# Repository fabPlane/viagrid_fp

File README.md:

# viagrid_fp
Viagrid example projects

This repository contains **10 introductory [Viagrid](https://viagrid.io) circuit board designs** covering fundamental PCB concepts. Each board is stored as a JSON file in the `boards/` directory and can be opened directly in Viagrid.

---

## Boards

| # | File | Description |
|---|------|-------------|
| 01 | [LED Blinker](boards/01_led_blinker.json) | 555-timer astable oscillator driving a red LED. Introduces RC timing, decoupling caps, and output current limiting. |
| 02 | [Push-Button LED](boards/02_push_button_led.json) | Tactile switch → current-limiting resistor → LED. The simplest possible complete circuit; includes a 100 nF debounce cap. |
| 03 | [3.3 V Buck Regulator](boards/03_buck_regulator_3v3.json) | XL4005 step-down switcher (5–40 V in → 3.3 V / 2 A out). Covers feedback dividers, flyback diode, and output capacitor sizing. |
| 04 | [Arduino Nano Breakout](boards/04_arduino_nano_breakout.json) | Clean breakout board exposing all Nano I/O pins on 0.1″ headers with barrel-jack power, decoupling caps, and M3 mounting holes. |
| 05 | [USB-C PD Sink](boards/05_usb_c_pd_sink.json) | CH224K PD negotiation IC requests 9 V or 12 V from a USB-C charger. Demonstrates CC resistors, TVS protection, and DIP-switch voltage selection. |
| 06 | [H-Bridge Motor Driver](boards/06_h_bridge_motor_driver.json) | L298N dual H-bridge for bidirectional DC motor or stepper control. Covers PWM inputs, flyback diodes, and isolated motor/logic power domains. |
| 07 | [Temp & Humidity Sensor Node](boards/07_temp_humidity_sensor_node.json) | ESP8266 (Wemos D1 Mini) + DHT22 with TP4056 LiPo charger and 3.3 V LDO. Teaches sensor pull-ups, battery management, and low-power Wi-Fi. |
| 08 | [RS-485 Isolated Transceiver](boards/08_rs485_isolated_transceiver.json) | MAX485 with PC817 opto-isolation for Modbus RTU. Shows bus termination, fail-safe bias resistors, and isolated power planes. |
| 09 | [Raspberry Pi HAT – GPIO & RTC](boards/09_rpi_hat_gpio_rtc.json) | MCP23017 I²C GPIO expander + DS3231 RTC + AT24C32 EEPROM on a standard RPi HAT form factor. Covers I²C addressing, battery backup, and HAT compliance. |
| 10 | [Class-D Audio Amplifier](boards/10_class_d_audio_amplifier.json) | PAM8403 stereo 3 W×2 amplifier with log-pot volume control, input coupling caps, and ferrite-bead EMI filters on speaker outputs. |

---

## How to use

1. Open [viagrid.io](https://viagrid.io) in your browser.
2. Create a new board or select *Import*.
3. Upload the desired `.json` file from the `boards/` directory.
4. The schematic, net list, and component placements will load automatically.

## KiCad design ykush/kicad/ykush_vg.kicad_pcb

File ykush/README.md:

# YKUSH-VG: 3-port switchable USB 2.0 hub on a Viagrid 9055 blank

A board that works like the [Yepkit YKUSH](https://www.yepkit.com/products/ykush), laid out for a
2-layer [Viagrid](https://github.com/opulo-inc/viagrid) 9055 blank.

- **Hub:** Terminus FE1.1s (SSOP-28). Upstream port is USB-C. Ports 1-3 go to the USB-A sockets,
  and port 4 goes to the control MCU.
- **Control:** WCH CH552G. The host sees it as a HID device. The plan is for its firmware to speak
  the YKUSH protocol, so `ykushcmd` works unchanged.
- **Port power:** one SY6280AAC current-limited switch per port. The CH552G drives each EN pin,
  and each EN has a 100k pull-down so the port stays off during boot.
- **Power:** from upstream VBUS, or from an external 5 V screw terminal. The two sources are
  diode-ORed onto `+5V_PORT`.

| File | What |
|---|---|
| `FEASIBILITY.md` | Why this is doable on Viagrid, and the risks |
| `kicad/ykush_vg.kicad_pro` / `.kicad_sch` | KiCad 10 project and schematic (generated) |
| `kicad/ykush_vg.kicad_sym`, `kicad/sym-lib-table` | Project symbol library (CH552G, SY6280AAC) |
| `kicad/ykush_vg_schematic.pdf` | PDF of the schematic |
| `kicad/bom.md`, `kicad/bom.csv` | BOM with Shopee/Lazada, AliExpress, DigiKey and JLCPCB columns |
| `kicad/nets.txt` | Netlist the generator intended |
| `tools/make_schematic.py` | **Source of truth.** Edit this, then regenerate |
| `tools/check_netlist.py` | Exports the netlist with kicad-cli and diffs it against `nets.txt` |
| `kicad/ykush_vg.kicad_pcb` | The PCB, generated by `tools/build_pcb.py` (see `pcb/LAYOUT.md`) |
| `firmware/` | CH552G firmware (SDCC), tests, host tool, udev rule |
| `fab/` | Laser DXFs, Gerbers, drill file, `holes_to_drill.csv`, placement file, previews |

```sh
cd tools && python3 make_schematic.py && python3 check_netlist.py
kicad-cli sch erc --severity-all ../kicad/ykush_vg.kicad_sch
```

Needs KiCad 10. The generator reads the KiCad 10 symbol libraries and then runs
`kicad-cli sch upgrade`, so the saved file is in KiCad's native format.

## Status
- [x] Schematic. Pinouts checked against the FE1.1s, CH552 and SY6280 datasheets, and against
  open-source boards.
- [x] BOM and sourcing
- [x] ERC in KiCad 10.0.6: 0 violations (all severities)
- [x] PCB layout on the Viagrid 9055 blank: fully routed. KiCad 10 DRC reports 0 errors,
  0 unconnected items and 0 schematic mismatches (details in `pcb/LAYOUT.md`).
- [x] Fabrication outputs in `fab/`: copper DXF for LightBurn, Gerbers, and the holes to drill
- [x] CH552 firmware (`firmware/`): YKUSH protocol with YKUSH USB IDs, so `ykushcmd` works.
  It builds to about 2.5 KB and passes descriptor, unit and `ykushcmd` end-to-end tests. It has not
  yet run on real hardware.
- [ ] Build and test a real board

## CH552G pin map (for the firmware)

| Function | CH552G pin |
|---|---|
| USB D+ / D- (hub port 4, Full-Speed) | P3.6 / P3.7 |
| EN port 1 (J2, left) | P1.4 |
| EN port 2 (J3, middle) | P3.3 |
| EN port 3 (J4, right) | P3.4 |
| Status LED (active high) | P3.2 |
| BOOT button (UDP pull-up at power-on) | P3.6 via 10k |

The EN pins are active high. Each has a 100k pull-down, so the ports stay off until the
firmware drives them.

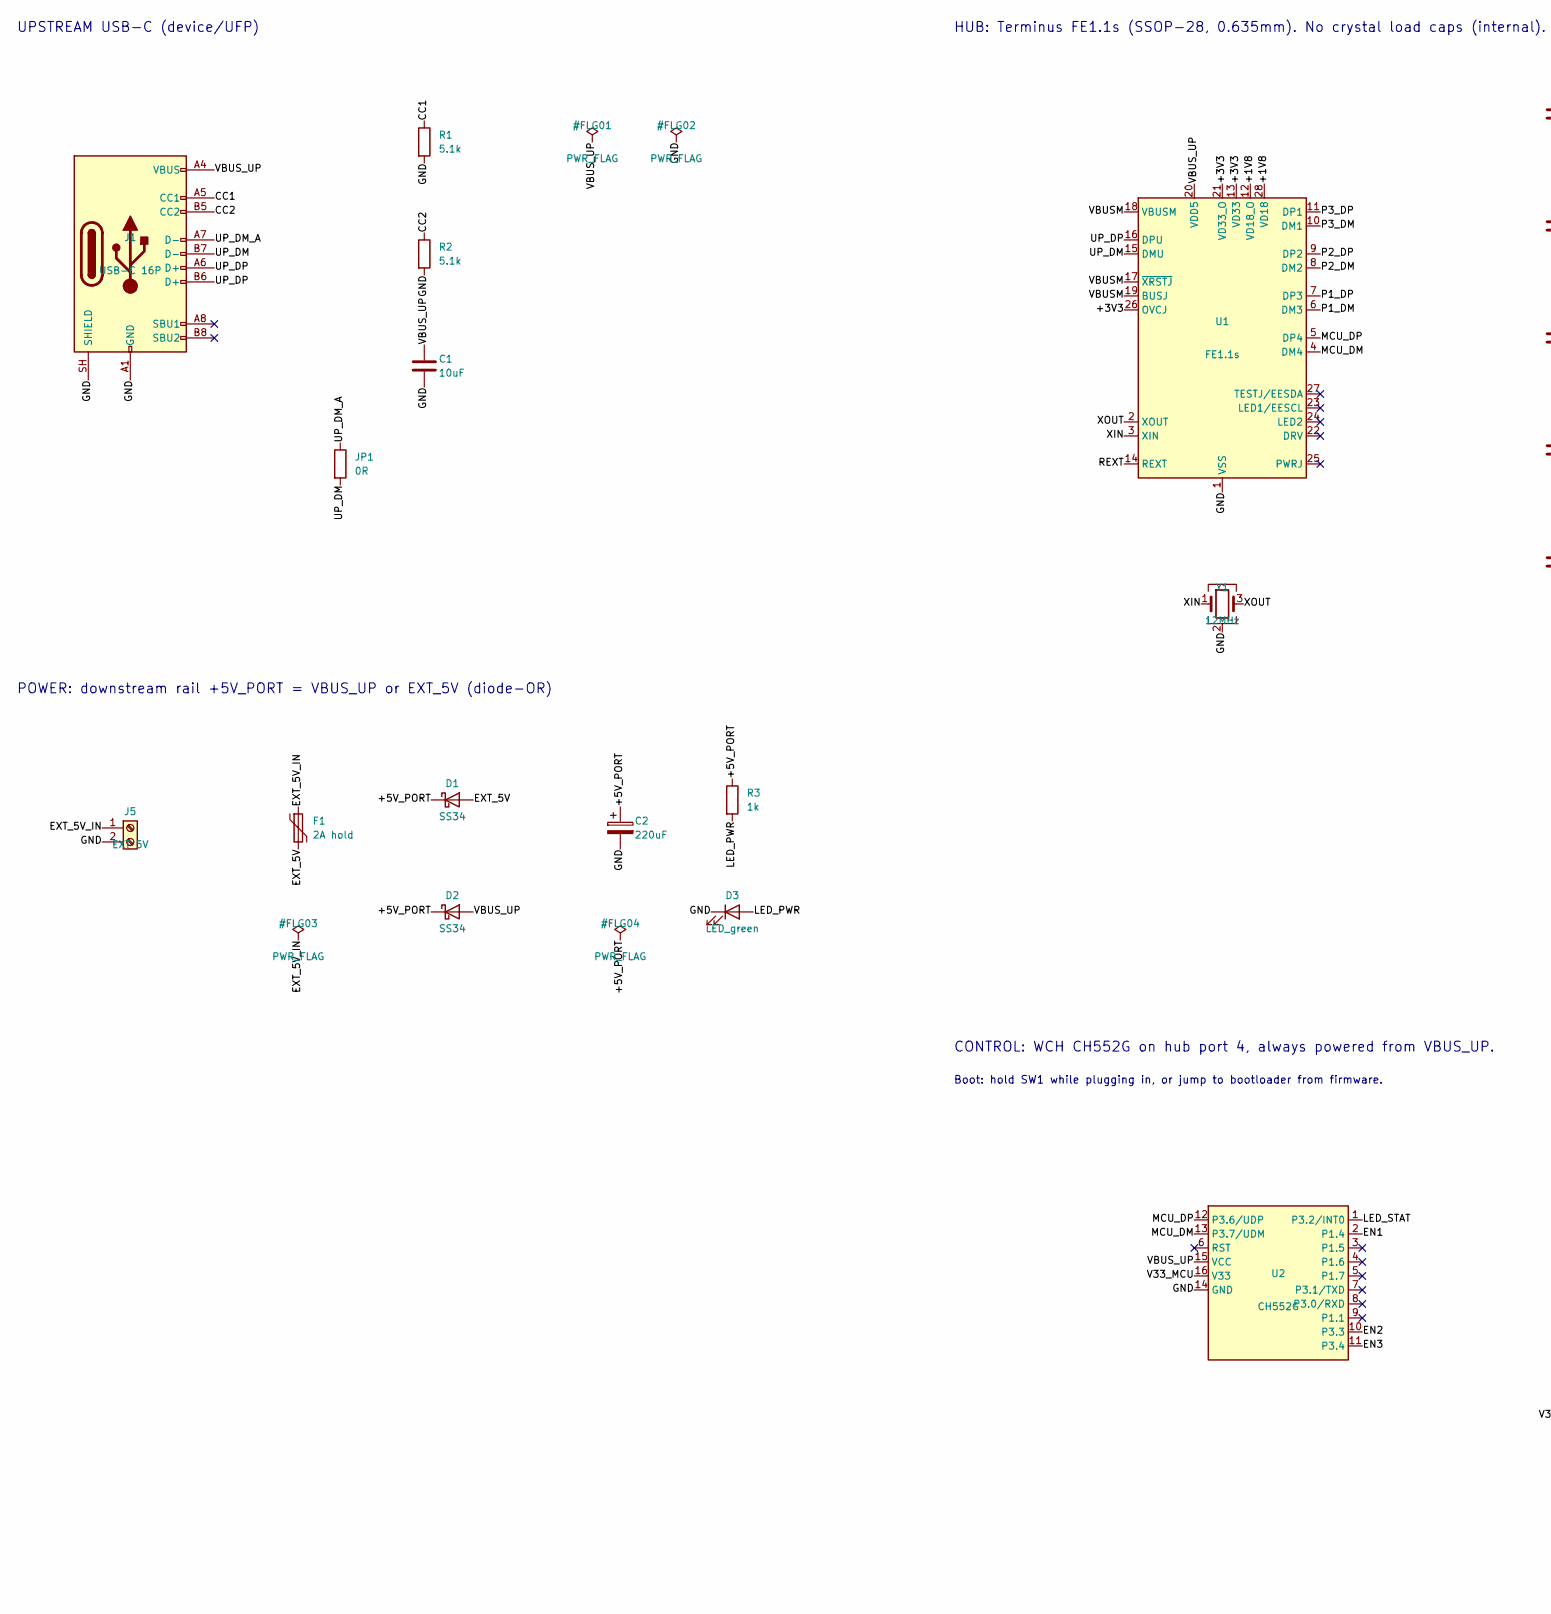
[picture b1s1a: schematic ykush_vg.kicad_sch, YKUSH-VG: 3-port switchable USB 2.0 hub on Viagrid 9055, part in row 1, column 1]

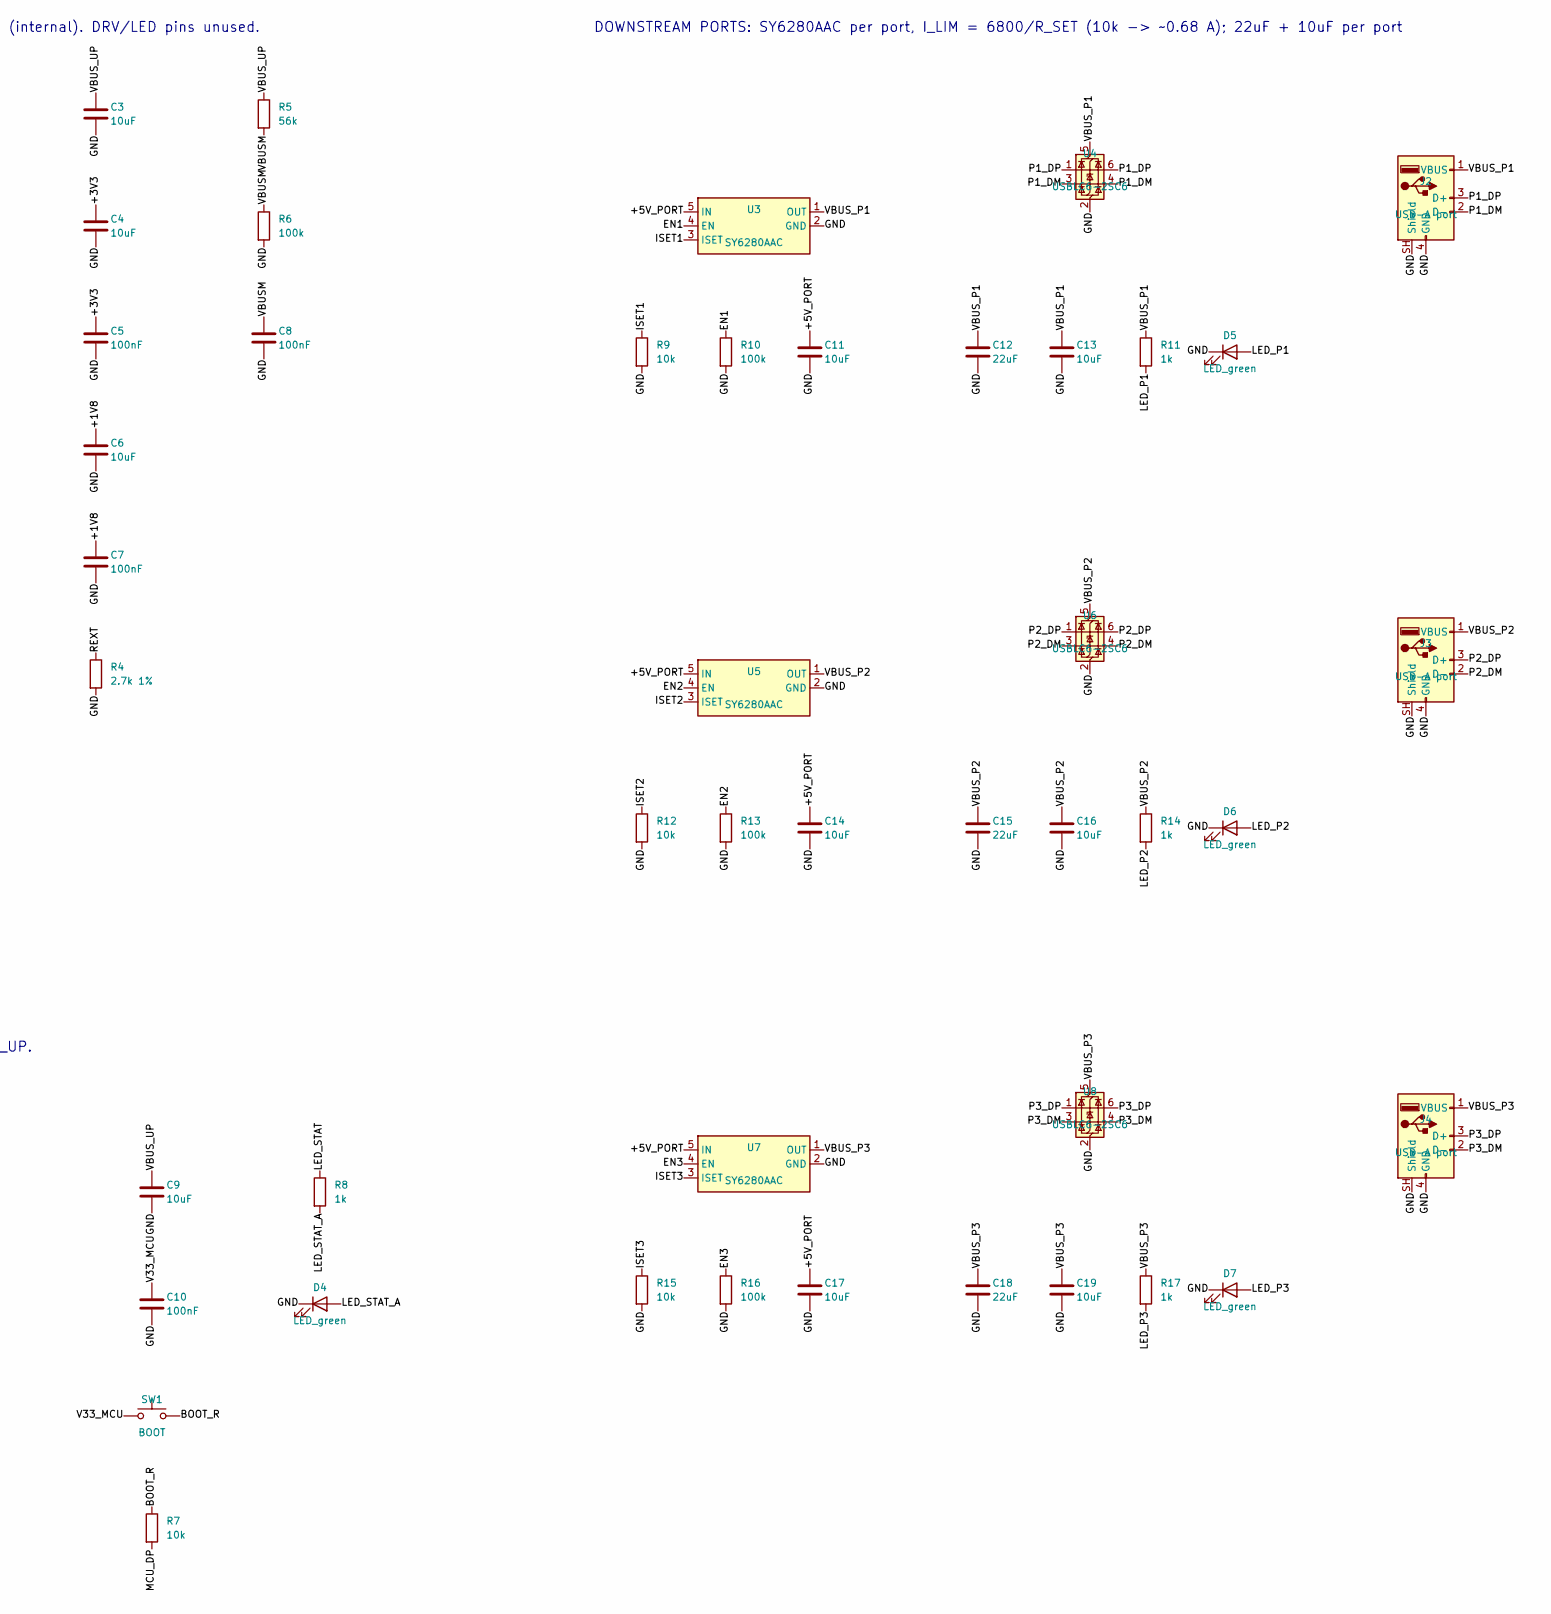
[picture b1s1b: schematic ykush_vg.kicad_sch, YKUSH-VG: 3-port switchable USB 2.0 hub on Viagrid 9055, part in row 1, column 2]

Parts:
C1, C3, C4, C6, C9, C11, C13, C14, C16, C17, C19: 10uF; C_0805_2012Metric
C2: 220uF; CP_Elec_6.3x7.7
C5, C7, C8, C10: 100nF; C_0603_1608Metric
C12, C15, C18: 22uF; C_1206_3216Metric
D1, D2: SS34; D_SMA
D3, D4, D5, D6, D7: LED_green; LED_0805_2012Metric
F1: 2A hold; Fuse_1812_4532Metric
J1: USB-C 16P; USB_C_Receptacle_HRO_TYPE-C-31-M-12
J2, J3, J4: USB-A port; USB_A_TE_292303-7_Horizontal
J5: EXT 5V; TerminalBlock_Phoenix_MKDS-1,5-2-5.08_1x02_P5.08mm_Horizont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
JP1: 0R; R_0603_1608Metric
R1, R2: 5.1k; R_0603_1608Metric
R3, R8, R11, R14, R17: 1k; R_0603_1608Metric
R4: 2.7k 1%; R_0603_1608Metric
R5: 56k; R_0603_1608Metric
R6, R10, R13, R16: 100k; R_0603_1608Metric
R7, R9, R12, R15: 10k; R_0603_1608Metric
SW1: BOOT; SW_Push_1P1T_XKB_TS-1187A
U1: FE1.1s; SSOP-28_3.9x9.9mm_P0.635mm
U2: CH552G; SOIC-16_3.9x9.9mm_P1.27mm
U3, U5, U7: SY6280AAC; SOT-23-5
U4, U6, U8: USBLC6-2SC6; SOT-23-6
Y1: 12MHz; Crystal_SMD_3225-4Pin_3.2x2.5mm

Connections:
/+1V8: C6.1, C7.1, U1.12 (VD18_O), U1.28 (VD18)
/+3V3: C4.1, C5.1, U1.13 (VD33), U1.21 (VD33_O), U1.26 (OVCJ)
/+5V_PORT: C2.1, C11.1, C14.1, C17.1, D1.1 (K), D2.1 (K), R3.1, U3.5 (IN), U5.5 (IN), U7.5 (IN)
/BOOT_R: R7.1, SW1.2
/CC1: J1.A5 (CC1), R1.1
/CC2: J1.B5 (CC2), R2.1
/EN1: R10.1, U2.2 (P1.4), U3.4 (EN)
/EN2: R13.1, U2.10 (P3.3), U5.4 (EN)
/EN3: R16.1, U2.11 (P3.4), U7.4 (EN)
/EXT_5V: D1.2 (A), F1.2
/EXT_5V_IN: F1.1, J5.1
/GND: C1.2, C2.2, C3.2, C4.2, C5.2, C6.2, C7.2, C8.2, C9.2, C10.2, C11.2, C12.2, C13.2, C14.2, C15.2, C16.2, C17.2, C18.2, C19.2, D3.1 (K), D4.1 (K), D5.1 (K), D6.1 (K), D7.1 (K), J1.A1 (GND), J1.A12 (GND), J1.B1 (GND), J1.B12 (GND), J1.SH (SHIELD), J2.4 (GND), J2.SH (Shield), J3.4 (GND), J3.SH (Shield), J4.4 (GND), J4.SH (Shield), J5.2, R1.2, R2.2, R4.2, R6.2, R9.2, R10.2, R12.2, R13.2, R15.2, R16.2, U1.1 (VSS), U2.14 (GND), U3.2 (GND), U4.2 (GND), U5.2 (GND), U6.2 (GND), U7.2 (GND), U8.2 (GND), Y1.2 (G), Y1.4 (G)
/ISET1: R9.1, U3.3 (ISET)
/ISET2: R12.1, U5.3 (ISET)
/ISET3: R15.1, U7.3 (ISET)
/LED_P1: D5.2 (A), R11.2
/LED_P2: D6.2 (A), R14.2
/LED_P3: D7.2 (A), R17.2
/LED_PWR: D3.2 (A), R3.2
/LED_STAT: R8.1, U2.1 (P3.2/INT0)
/LED_STAT_A: D4.2 (A), R8.2
/MCU_DM: U1.4 (DM4), U2.13 (P3.7/UDM)
/MCU_DP: R7.2, U1.5 (DP4), U2.12 (P3.6/UDP)
/P1_DM: J2.2 (D-), U1.6 (DM3), U4.3 (I/O2), U4.4 (I/O2)
/P1_DP: J2.3 (D+), U1.7 (DP3), U4.1 (I/O1), U4.6 (I/O1)
/P2_DM: J3.2 (D-), U1.8 (DM2), U6.3 (I/O2), U6.4 (I/O2)
/P2_DP: J3.3 (D+), U1.9 (DP2), U6.1 (I/O1), U6.6 (I/O1)
/P3_DM: J4.2 (D-), U1.10 (DM1), U8.3 (I/O2), U8.4 (I/O2)
/P3_DP: J4.3 (D+), U1.11 (DP1), U8.1 (I/O1), U8.6 (I/O1)
/REXT: R4.1, U1.14 (REXT)
/UP_DM: J1.B7 (D-), JP1.2, U1.15 (DMU)
/UP_DM_A: J1.A7 (D-), JP1.1
/UP_DP: J1.A6 (D+), J1.B6 (D+), U1.16 (DPU)
/V33_MCU: C10.1, SW1.1, U2.16 (V33)
/VBUSM: C8.1, R5.2, R6.1, U1.17 (~XRSTJ), U1.18 (VBUSM), U1.19 (BUSJ)
/VBUS_P1: C12.1, C13.1, J2.1 (VBUS), R11.1, U3.1 (OUT), U4.5 (VBUS)
/VBUS_P2: C15.1, C16.1, J3.1 (VBUS), R14.1, U5.1 (OUT), U6.5 (VBUS)
/VBUS_P3: C18.1, C19.1, J4.1 (VBUS), R17.1, U7.1 (OUT), U8.5 (VBUS)
/VBUS_UP: C1.1, C3.1, C9.1, D2.2 (A), J1.A4 (VBUS), J1.A9 (VBUS), J1.B4 (VBUS), J1.B9 (VBUS), R5.1, U1.20 (VDD5), U2.15 (VCC)
/XIN: U1.3 (XIN), Y1.1
/XOUT: U1.2 (XOUT), Y1.3

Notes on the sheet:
HUB: Terminus FE1.1s (SSOP-28, 0.635mm). No crystal load caps (internal). DRV/LED pins unused.
UPSTREAM USB-C (device/UFP)
POWER: downstream rail +5V_PORT = VBUS_UP or EXT_5V (diode-OR)
DOWNSTREAM PORTS: SY6280AAC per port, I_LIM = 6800/R_SET (10k -> ~0.68 A); 22uF + 10uF per port
Boot: hold SW1 while plugging in, or jump to bootloader from firmware.
CONTROL: WCH CH552G on hub port 4, always powered from VBUS_UP.

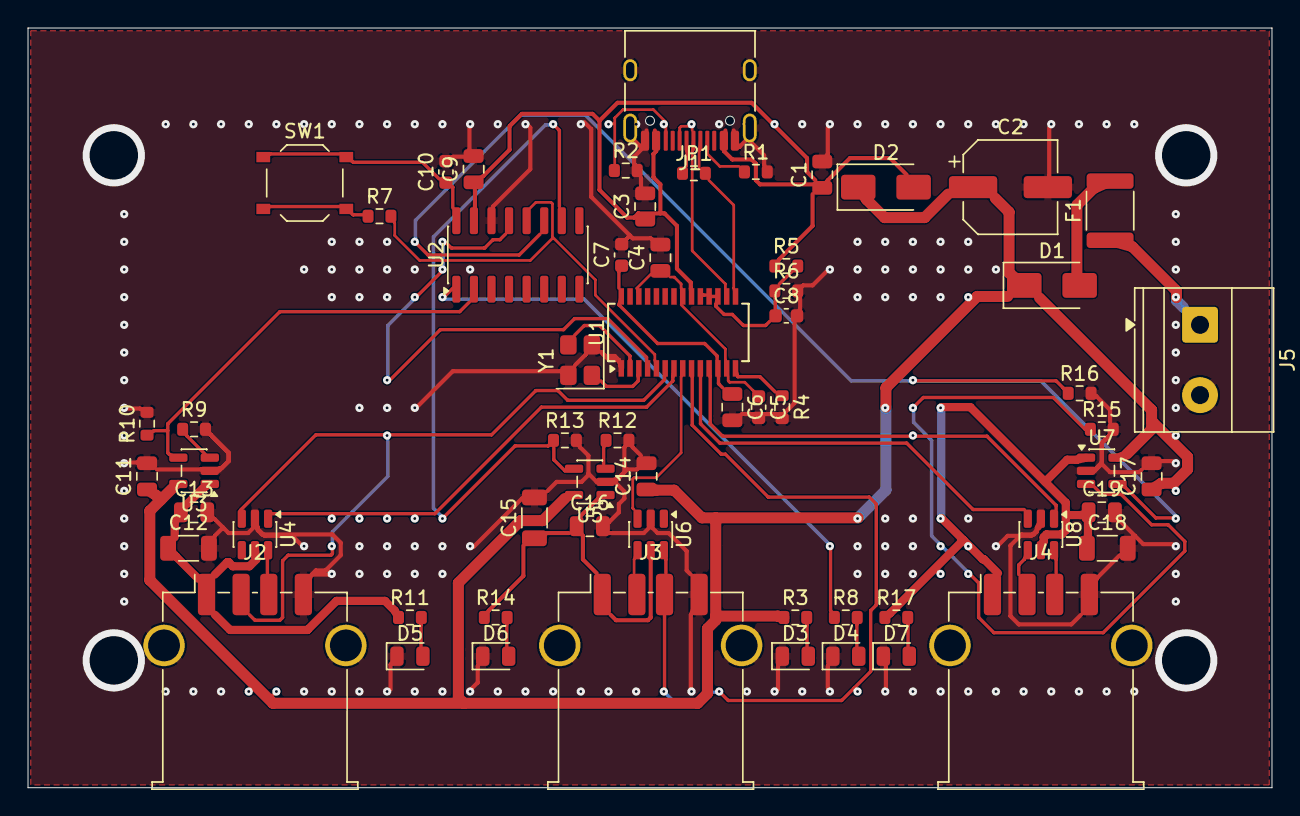
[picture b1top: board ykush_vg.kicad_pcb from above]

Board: 2 copper layers, 89.9 x 54.9 mm, 60 parts (0 on the bottom side), 41 nets.

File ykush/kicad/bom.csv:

#,Refs,Qty,Part,Footprint,Shopee / Lazada (Thailand),AliExpress,DigiKey,JLCPCB (LCSC #),JLC type,Notes
1,U1,1,Terminus FE1.1S-BSOP28 (USB 2.0 HS 4-port hub),SSOP-28_3.9x9.9mm_P0.635mm,YES - Shopee TH (5 pcs),YES,"NO (alt: Microchip USB2514B-AEZC-TR, QFN-36)",C9359,Extended,Buy genuine Rev B (FE1.1S-BSOP28). Cross-border seller: 1-2 weeks.
2,U2 U5 U7 U9,4,ST USBLC6-2SC6 USB ESD array,SOT-23-6,"YES - Shopee TH, Lazada TH",YES,497-5235-1-ND,C7519,Extended,
3,U3,1,"WCH CH552G (SOP-16 MCU, USB device)",SOIC-16_3.9x9.9mm_P1.27mm,YES - Shopee TH (variant in WCH multi-chip listing),YES,NO (alt: PIC16F1455-I/SL; needs different firmware),C111292,Extended,Blank chips boot into the USB bootloader.
4,U4 U6 U8,3,Silergy SY6280AAC load switch,SOT-23-5,NO (MT9700 is on Shopee TH; verify pinout before substituting),YES,"NO (alt: TI TPS2051BDBVR, different pinout)",C55136,Extended,Order from AliExpress/LCSC. Not SY6280AAAC (C207620).
5,Y1,1,YXC X322512MSB4SI 12 MHz 3225 4-pad,Crystal_SMD_3225-4Pin_3.2x2.5mm,NO (only HC-49 seen),YES,Abracon ABM8-12.000MHZ-B2-T (535-9826-1-ND),C9002,Basic,"Passive crystal, not an oscillator. FE1.1s has internal load caps."
6,J1,1,HRO TYPE-C-31-M-12 (USB 2.0 16-pin),USB_C_Receptacle_HRO_TYPE-C-31-M-12,"YES - Shopee TH (TYPE-C-31-M-12), Lazada TH (16P)",YES,"NO (alt: GCT USB4105-GF-A, 2073-USB4105-GF-ACT-ND)",C165948,Extended,Shell pegs need drilled holes on a Viagrid.
7,J2 J3 J4,3,"TE 292303-7 USB-A receptacle, right angle, SMT signal pins",USB_A_TE_292303-7_Horizontal,NO (TH has generic THT 4-pin 90deg; different footprint),LIKELY,TE 292303-7,(search LCSC),Extended,SMT signal pads keep the Viagrid build simple; only the 2 shell tabs need holes.
8,J5,1,Screw terminal 2P 5.08 mm (KF301-2P),"TerminalBlock_Phoenix_MKDS-1,5-2-5.08_1x02_P5.08mm_Horizontal","YES - Shopee TH, Lazada TH, Cybertice, MyArduino",YES,Phoenix 1935161 (277-1667-ND),C474881,Extended,"THT: drill 2 holes, solder from the bottom."
9,SW1,1,Tactile switch 5.1x5.1 mm SMD (XKB TS-1187A-B-A-B),SW_Push_1P1T_XKB_TS-1187A,NO (only 3x4 / 4.5x4.5 / 6x6 seen),YES,C&K PTS810 SJM 250 SMTR LFS,C318884,Basic,Hold while plugging in = CH552 bootloader.
10,F1,1,"PTC resettable fuse 1812, 2 A hold",Fuse_1812_4532Metric,YES - Shopee TH (PPTC kit incl. 1812),YES,Littelfuse 1812L200/12DR,C315901,Extended,
11,D1 D2,2,"SS34 Schottky 3 A 40 V, SMA",D_SMA,YES - Shopee TH (ships from Thailand),YES,Vishay SSA34-E3/61T,C8678,Basic,
12,D3 D4 D5 D6 D7,5,LED green 0805,LED_0805_2012Metric,"YES - Shopee TH, Lazada TH (0805 colour kits)",YES,Lite-On LTST-C171GKT,C2297,Basic,
13,C1 C3 C4 C6 C9 C11 C13 C14 C16 C17 C19,11,MLCC 10 uF 25 V X5R 0805,C_0805_2012Metric,YES - Lazada TH (0805 kit),YES,Samsung CL21A106KAYNNNC,C15850,Basic,
14,C2,1,Alu electrolytic 220 uF 10 V SMD 6.3x7.7 mm,CP_Elec_6.3x7.7,"YES - Shopee TH (220u/16V 6.3x7.7), Lazada TH",YES,Panasonic EEE-FK1A221P (verify),(pick on LCSC),Extended,Bulk on +5V_PORT.
15,C5 C7 C8 C10,4,MLCC 100 nF 50 V X7R 0603,C_0603_1608Metric,YES - Shopee TH (0603 kit),YES,Yageo CC0603KRX7R9BB104,C14663,Basic,
16,C12 C15 C18,3,MLCC 22 uF 25 V X5R 1206,C_1206_3216Metric,LIKELY,YES,Samsung CL31A226KAHNNNE,C12891,Basic,Per-port bulk. USB 2.0 asks for 120 uF per port; SY6280 soft-start limits inrush instead.
17,R1 R2,2,Resistor 5.1 k 1% 0603,R_0603_1608Metric,"YES - Shopee TH (0603 kit, 33 values x 20)",YES,generic,C23186,Basic,USB-C CC
18,R3 R8 R11 R14 R17,5,Resistor 1 k 1% 0603,R_0603_1608Metric,"YES - Shopee TH (0603 kit, 33 values x 20)",YES,generic,C21190,Basic,
19,R4,1,Resistor 2.7 k 1% 0603 (FE1.1s REXT),R_0603_1608Metric,"YES - Shopee TH (0603 kit, 33 values x 20)",YES,generic,C13167,Basic,Must be 1%.
20,R5,1,Resistor 56 k 1% 0603,R_0603_1608Metric,"YES - Shopee TH (0603 kit, 33 values x 20)",YES,generic,C23206,Basic,VBUSM divider top (also drives XRSTJ/BUSJ).
21,R6 R10 R13 R16,4,Resistor 100 k 1% 0603,R_0603_1608Metric,"YES - Shopee TH (0603 kit, 33 values x 20)",YES,generic,C25803,Basic,
22,R7 R9 R12 R15,4,Resistor 10 k 1% 0603,R_0603_1608Metric,"YES - Shopee TH (0603 kit, 33 values x 20)",YES,generic,C25804,Basic,ISET: 10k = ~0.68 A limit; 6.8k (C23212) = ~1 A.
23,JP1,1,Resistor 0 R 0603 (jumper over USB-C D- trace),R_0603_1608Metric,"YES - Shopee TH (0603 kit, 33 values x 20)",YES,generic,C21189,Basic,Board jumper: USB-C D+ pads are interleaved with D-.
24,-,1,"Viagrid 9055 Standard blank (90x55 mm, 2-layer, ENIG)",-,NO,NO,NO,-,-,"Opulo (opulo.io), or have JLCPCB/PCBWay make it from the open-source Viagrid files."
25,-,1,Enclosure Hammond 1591XXB (optional),-,NO (generic ABS boxes only),LIKELY (clones),HM1038-ND (1591XXBBK),-,-,TME Thailand lists Hammond (ships from abroad).
